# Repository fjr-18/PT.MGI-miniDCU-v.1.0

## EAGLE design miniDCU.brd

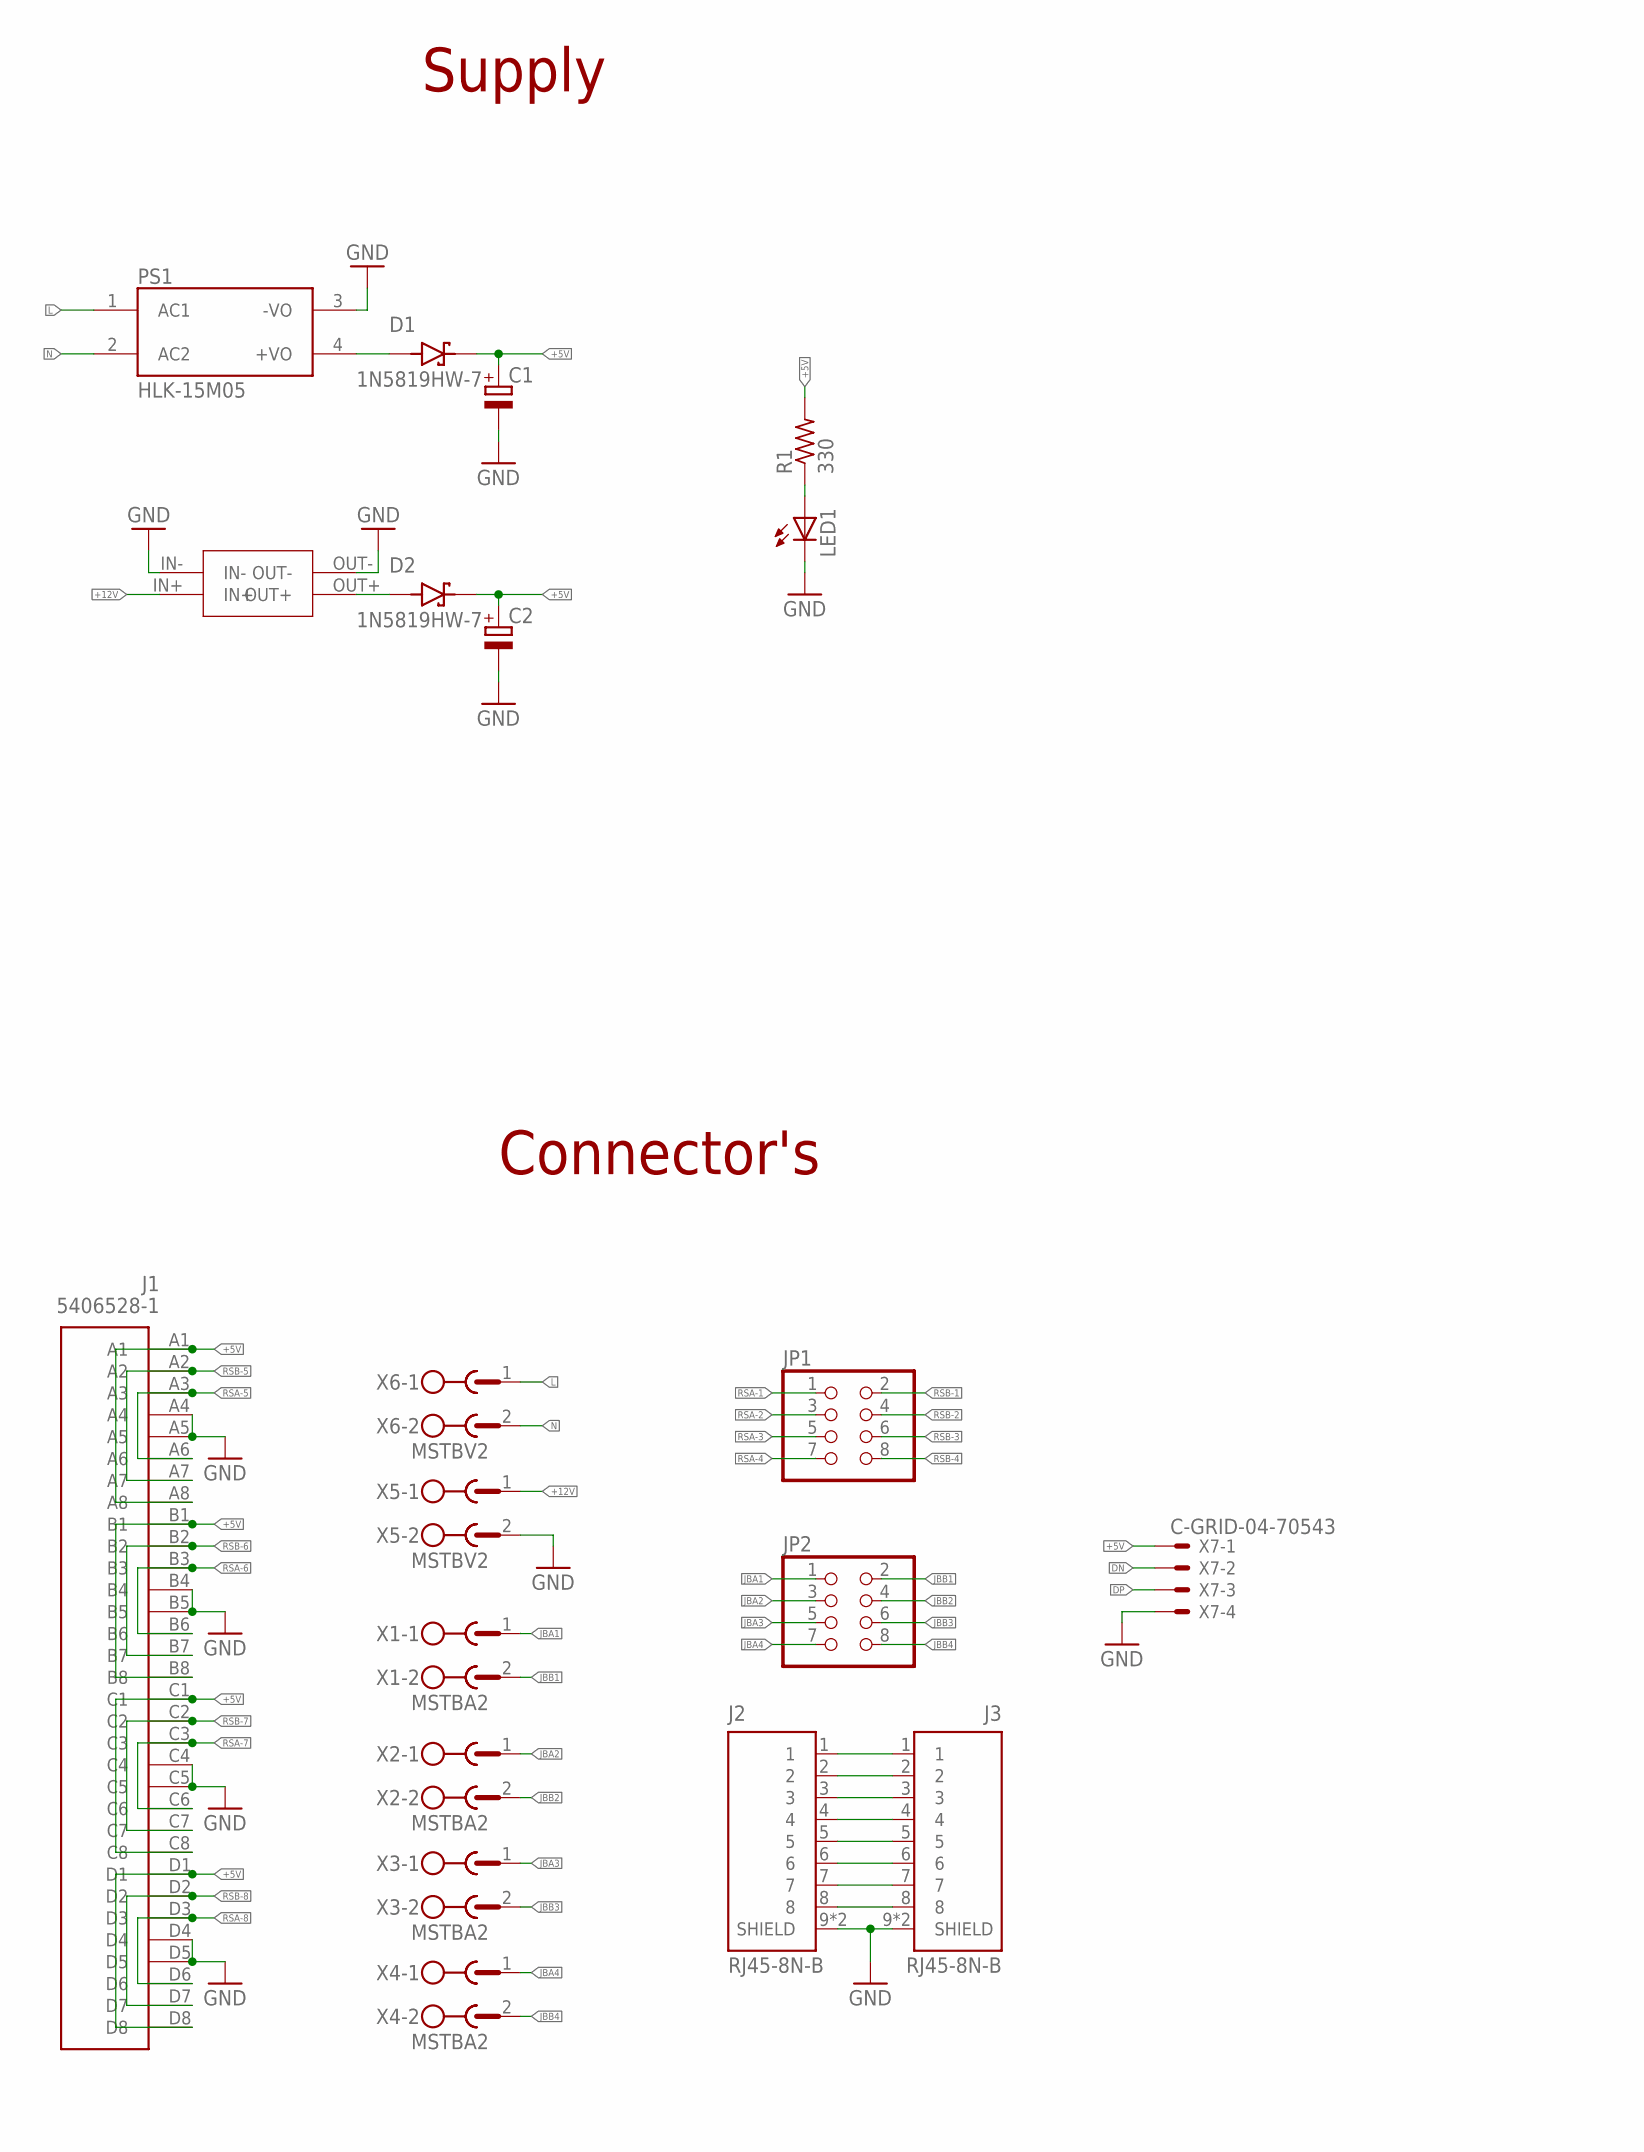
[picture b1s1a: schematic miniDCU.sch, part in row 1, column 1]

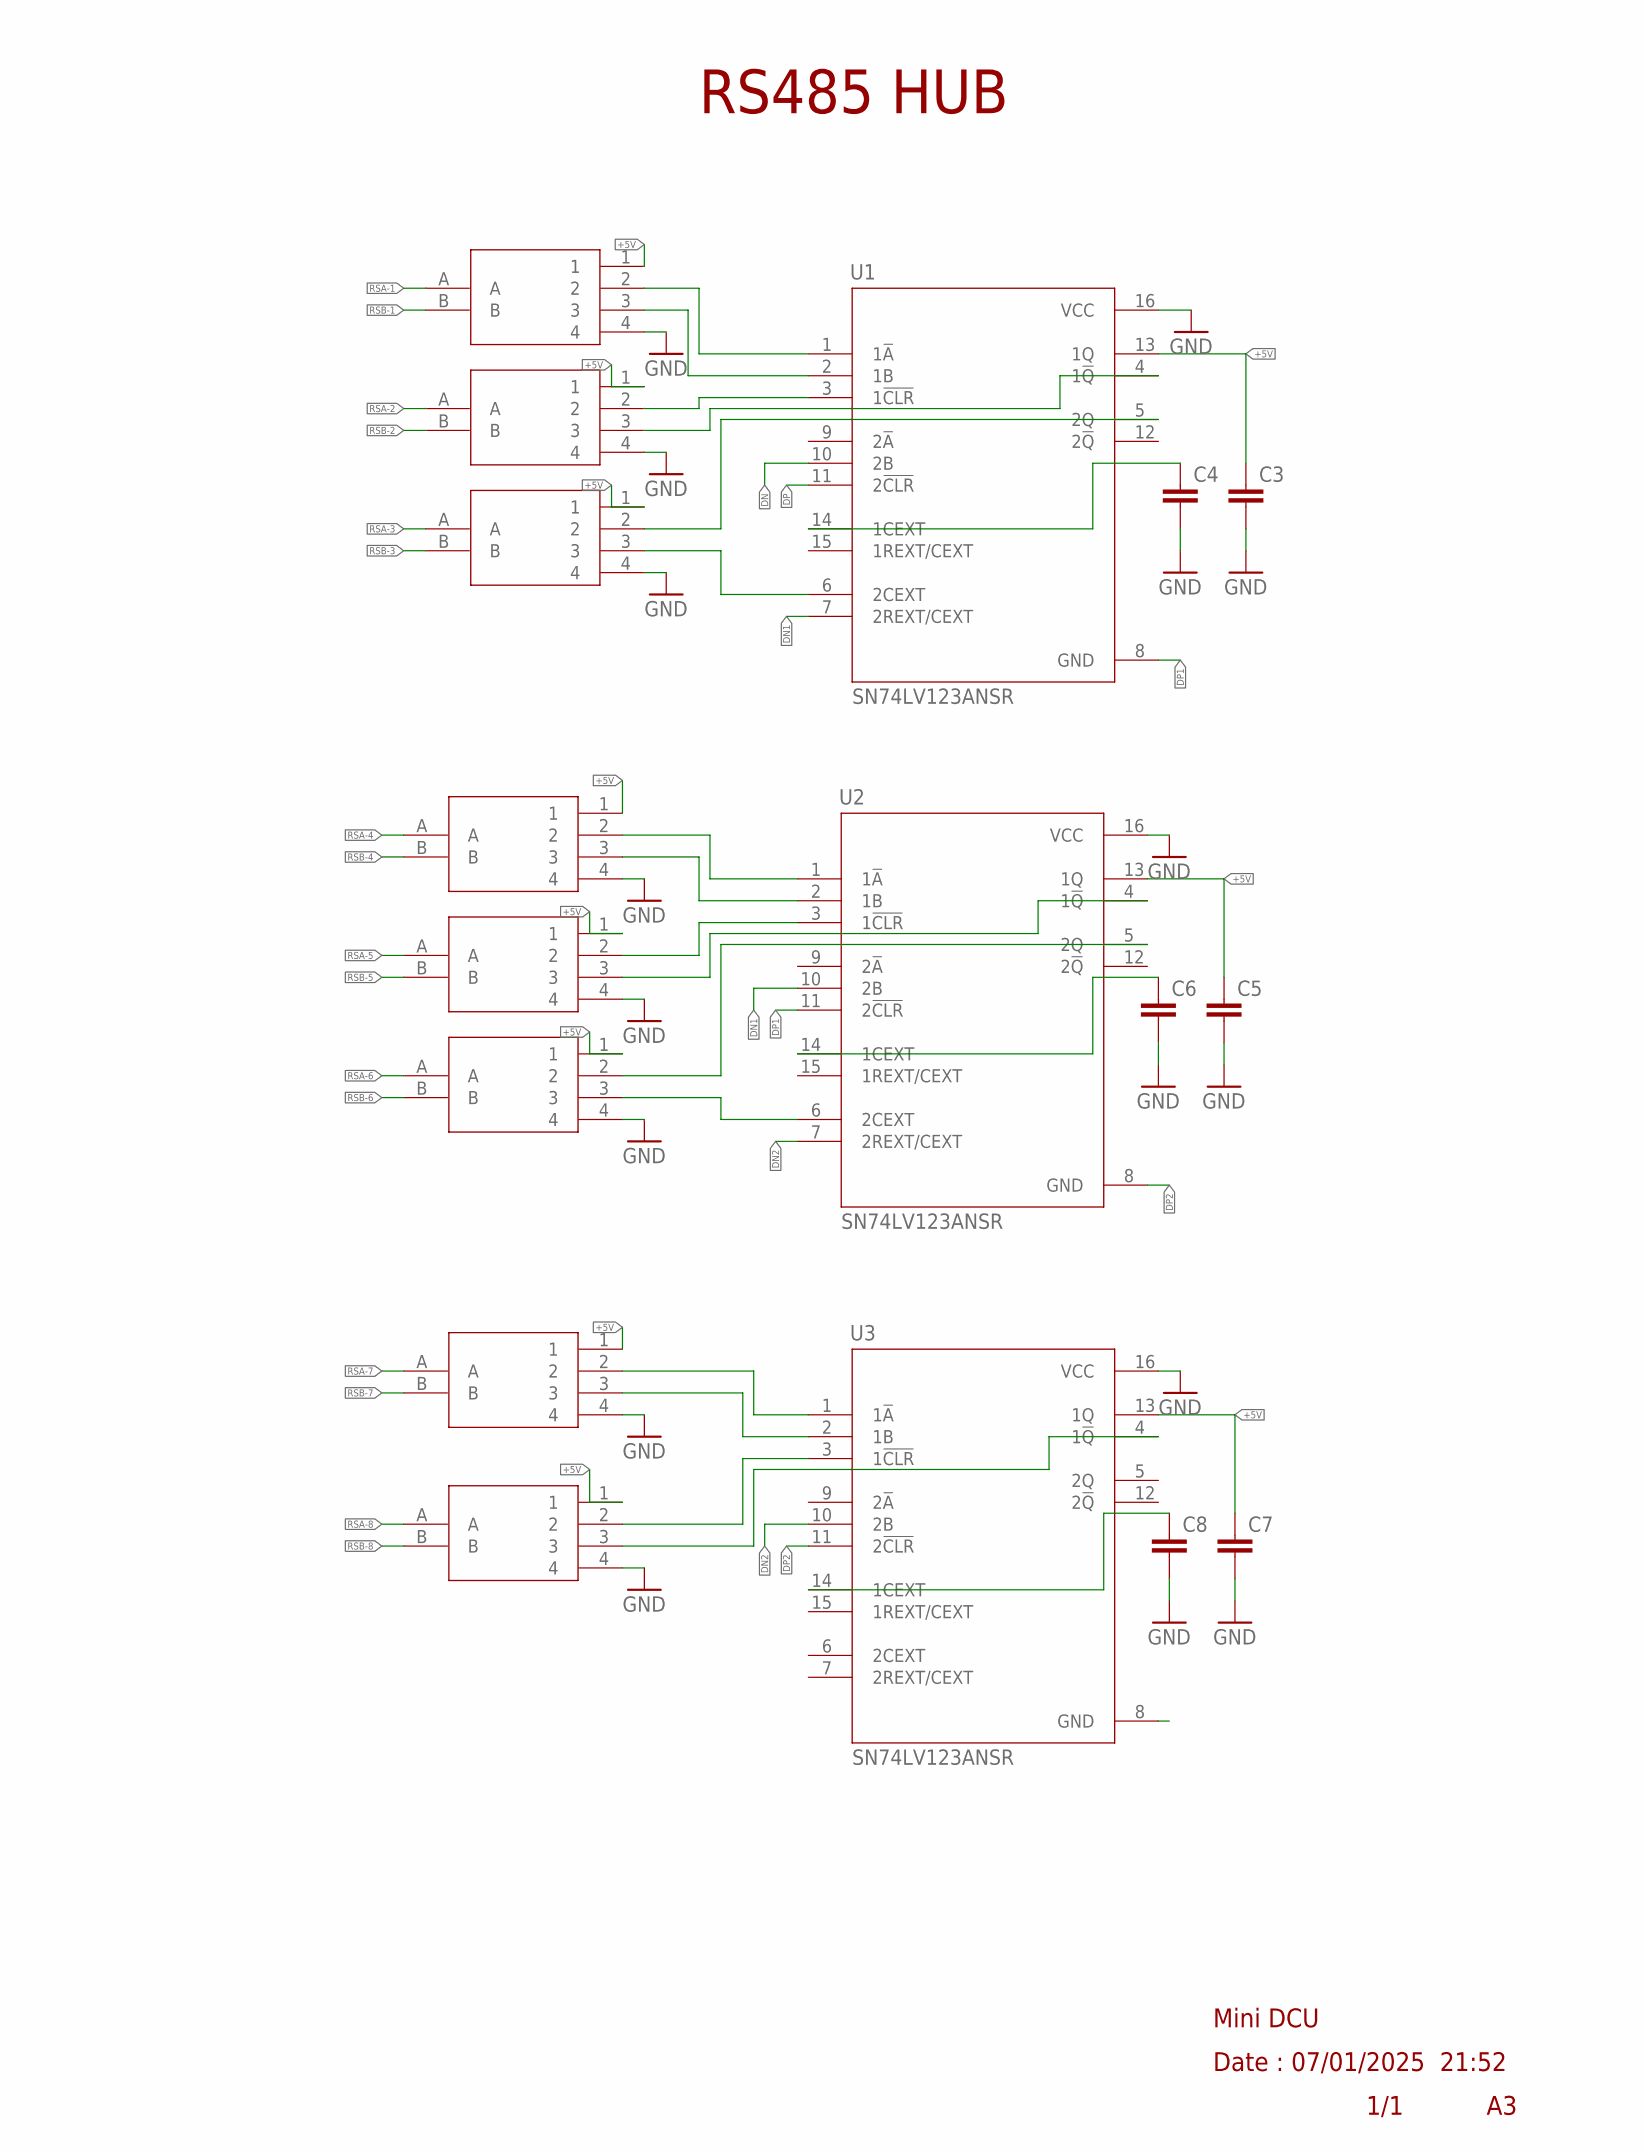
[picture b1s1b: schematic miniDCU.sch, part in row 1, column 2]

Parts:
C1, C2: CPOL-EU153CLV-0505; 153CLV-0505
C3, C4, C5, C6, C7, C8: C-EUC0603K; C0603K
D1, D2: 1N5819HW-7; SOD3715X145N
J1: 5406528-1
J2, J3: RJ45-8N-B; TE_RJ45-8N-B
JP1, JP2: PINHD-2X4; 2X04
LED1: LED3MM
MINI1: MINI360
PS1: HLK-15M05; CONV_HLK-15M05
R1: 330; M0805
U1, U2, U3: SN74LV123ANSR; SOIC127P780X200-16N
USB2RS1, USB2RS2, USB2RS3, USB2RS4, USB2RS5, USB2RS6, USB2RS7, USB2RS8: USB2RS485
X1, X2, X3, X4: MSTBA2
X5, X6: MSTBV2
X7: C-GRID-04-70543; 70543-04

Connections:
+5V: C1.+, C2.+, C3.1, C5.1, C7.1, D1.C (K), D2.C (K), J1.A1, J1.A8, J1.B1, J1.B8, J1.C1, J1.C8, J1.D1, J1.D8, R1.2, U1.13 (1Q), U2.13 (1Q), U3.13 (1Q), USB2RS1.1, USB2RS2.1, USB2RS3.1, USB2RS4.1, USB2RS5.1, USB2RS6.1, USB2RS7.1, USB2RS8.1, X7.1
+12V: MINI1.IN+, X5.1
DN: U1.10 (2B), X7.2
DN1: U1.7 (2REXT/CEXT), U2.10 (2B)
DN2: U2.7 (2REXT/CEXT), U3.10 (2B)
DP: U1.11 (2!CLR), X7.3
DP1: U1.8 (GND), U2.11 (2!CLR)
DP2: U2.8 (GND), U3.11 (2!CLR)
GND: C1.-, C2.-, C3.2, C4.2, C5.2, C6.2, C7.2, C8.2, J1.A4, J1.A5, J1.B4, J1.B5, J1.C4, J1.C5, J1.D4, J1.D5, J2.9 (SHIELD), J2.10 (SHIELD), J3.9 (SHIELD), J3.10 (SHIELD), LED1.K (C), MINI1.IN-, MINI1.OUT-, PS1.3 (-VO), U1.16 (VCC), U2.16 (VCC), U3.16 (VCC), USB2RS1.4, USB2RS2.4, USB2RS3.4, USB2RS4.4, USB2RS5.4, USB2RS6.4, USB2RS7.4, USB2RS8.4, X5.2, X7.4
JBA1: JP2.1, X1.1
JBA2: JP2.3, X2.1
JBA3: JP2.5, X3.1
JBA4: JP2.7, X4.1
JBB1: JP2.2, X1.2
JBB2: JP2.4, X2.2
JBB3: JP2.6, X3.2
JBB4: JP2.8, X4.2
L: PS1.1 (AC1), X6.1
N: PS1.2 (AC2), X6.2
unnamed: D1.A, PS1.4 (+VO)
unnamed: J2.1, J3.1
unnamed: D2.A, MINI1.OUT+
unnamed: J2.2, J3.2
unnamed: J2.3, J3.3
unnamed: J2.4, J3.4
unnamed: LED1.A, R1.1
unnamed: J2.5, J3.5
unnamed: J2.6, J3.6
unnamed: J2.7, J3.7
unnamed: J2.8, J3.8
unnamed: U1.1 (1!A), USB2RS1.2
unnamed: U1.2 (1B), USB2RS1.3
unnamed: U1.3 (1!CLR), USB2RS2.2
unnamed: U1.4 (1!Q), USB2RS2.3
unnamed: U1.5 (2Q), USB2RS3.2
unnamed: U1.6 (2CEXT), USB2RS3.3
unnamed: U2.1 (1!A), USB2RS5.2
unnamed: U2.2 (1B), USB2RS5.3
unnamed: U2.3 (1!CLR), USB2RS6.2
unnamed: U2.4 (1!Q), USB2RS6.3
unnamed: U2.5 (2Q), USB2RS7.2
unnamed: U2.6 (2CEXT), USB2RS7.3
unnamed: U3.1 (1!A), USB2RS4.2
unnamed: U3.2 (1B), USB2RS4.3
unnamed: U3.3 (1!CLR), USB2RS8.2
unnamed: U3.4 (1!Q), USB2RS8.3
unnamed: C4.1, U1.14 (1CEXT)
unnamed: C8.1, U3.14 (1CEXT)
unnamed: C6.1, U2.14 (1CEXT)
RSA-1: JP1.1, USB2RS1.A
RSA-2: JP1.3, USB2RS2.A
RSA-3: JP1.5, USB2RS3.A
RSA-4: JP1.7, USB2RS5.A
RSA-5: J1.A3, J1.A6, USB2RS6.A
RSA-6: J1.B3, J1.B6, USB2RS7.A
RSA-7: J1.C3, J1.C6, USB2RS4.A
RSA-8: J1.D3, J1.D6, USB2RS8.A
RSB-1: JP1.2, USB2RS1.B
RSB-2: JP1.4, USB2RS2.B
RSB-3: JP1.6, USB2RS3.B
RSB-4: JP1.8, USB2RS5.B
RSB-5: J1.A2, J1.A7, USB2RS6.B
RSB-6: J1.B2, J1.B7, USB2RS7.B
RSB-7: J1.C2, J1.C7, USB2RS4.B
RSB-8: J1.D2, J1.D7, USB2RS8.B

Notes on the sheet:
Mini DCU
Date : 07/01/2025 21:52
1/1
Supply
Connector's
RS485 HUB

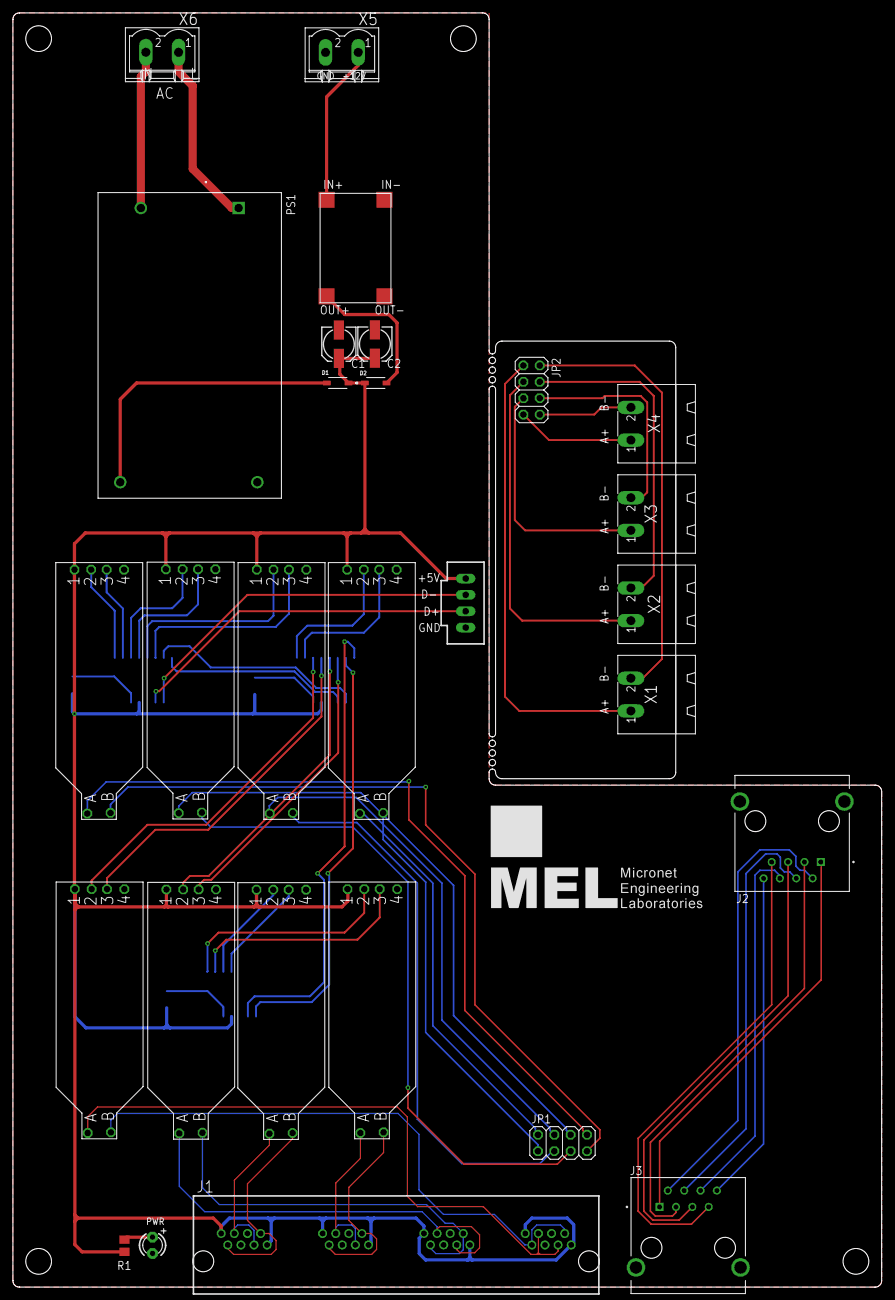
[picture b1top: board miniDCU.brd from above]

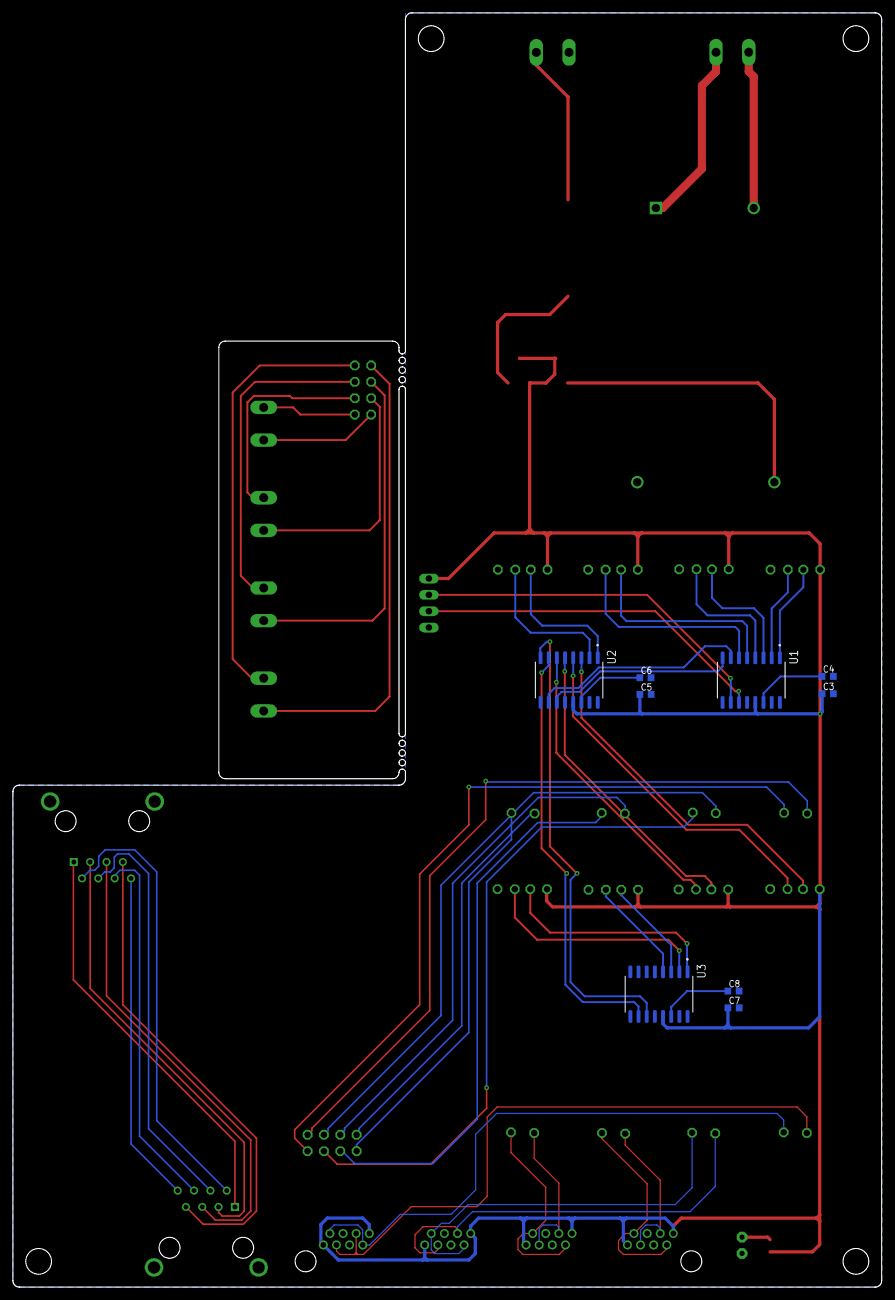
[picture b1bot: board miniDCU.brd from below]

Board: 2 copper layers, 135.0 x 198.0 mm, 37 parts (9 on the bottom side), 65 nets.
